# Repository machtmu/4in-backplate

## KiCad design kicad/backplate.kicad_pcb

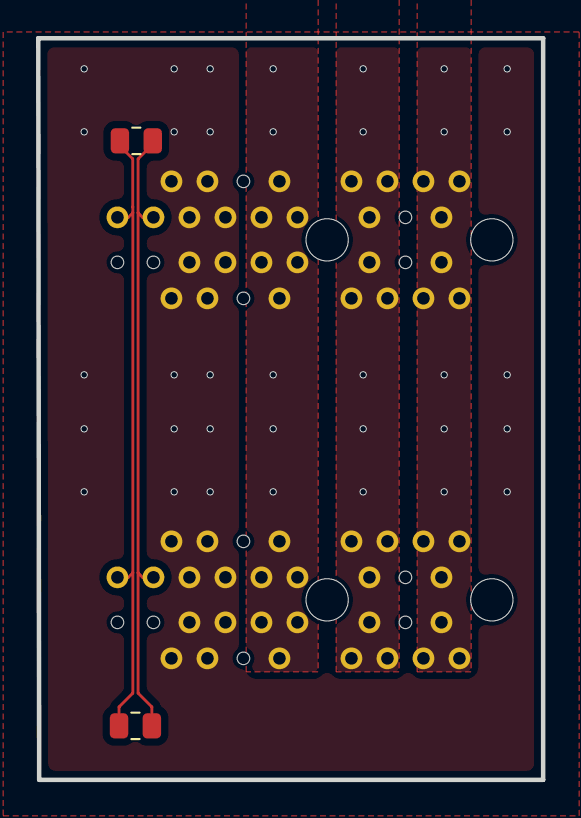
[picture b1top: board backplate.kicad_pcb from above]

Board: 2 copper layers, 28.0 x 41.2 mm, 4 parts (0 on the bottom side), 6 nets.

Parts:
J1, J1#2: 10018784-10210TLF; AMPHENOL_10018784-10210TLF
R1, R2: 120; R_0805_2012Metric

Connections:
+3.3V: J1.A9, J1.A10, J1.A11, J1.B9, J1.B10, J1.B11, J1#2.A9, J1#2.A10, J1#2.A11, J1#2.B9, J1#2.B10, J1#2.B11
+5V: J1.A12, J1.A13, J1.A14, J1.B12, J1.B13, J1.B14, J1#2.A12, J1#2.A13, J1#2.A14, J1#2.B12, J1#2.B13, J1#2.B14
+7.4V: J1.A16, J1.A17, J1.A18, J1.B16, J1.B17, J1.B18, J1#2.A16, J1#2.A17, J1#2.A18, J1#2.B16, J1#2.B17, J1#2.B18
CANN: J1.A3, J1#2.A3, R1.2, R2.2
CANP: J1.A1, J1#2.A1, R1.1, R2.1
GND: J1.A4, J1.A5, J1.A6, J1.A7, J1.B4, J1.B5, J1.B6, J1.B7, J1#2.A4, J1#2.A5, J1#2.A6, J1#2.A7, J1#2.B4, J1#2.B5, J1#2.B6, J1#2.B7

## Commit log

2025-10-04 modified backplate to 2 PCIe
2025-11-21 Update images
2025-11-23 remove old test files
